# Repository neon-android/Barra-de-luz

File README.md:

# PCB-Mini85-V1.0 
## Placa de control de cuatro pines de entrada y una salida a relevador con funcion corte de 12v o relevador usual
### Controlada por at timy 85 o at tiny 13

# Pin out

## Fabricacion
[Mini-85-V1.0.zip](https://github.com/user-attachments/files/15755527/Mini-85-V1.0.zip)

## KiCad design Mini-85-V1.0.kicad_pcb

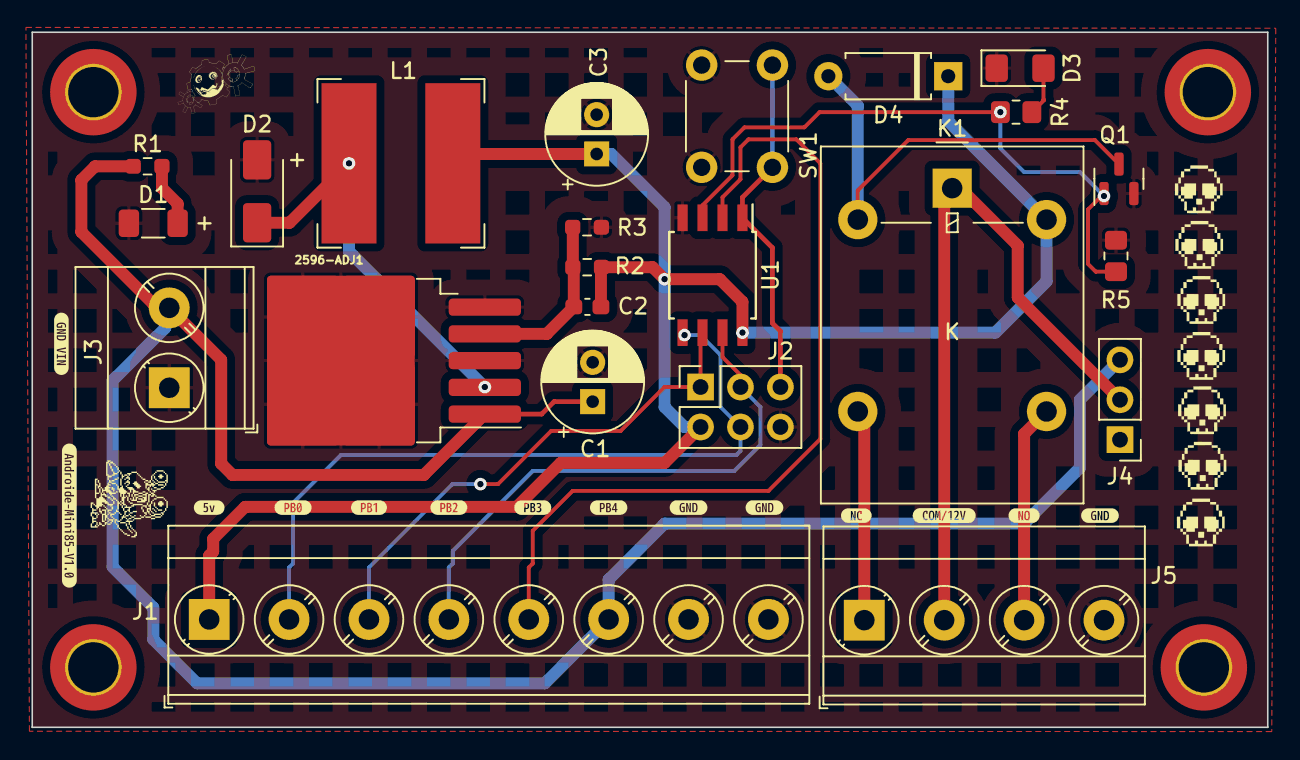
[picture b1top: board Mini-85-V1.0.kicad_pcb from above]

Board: 2 copper layers, 78.6 x 44.2 mm, 41 parts (0 on the bottom side), 17 nets.

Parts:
2596-ADJ1: REGULADOR ADJ; TO-263-5_TabPin3
C1: 470uf 35v; CP_Radial_D6.3mm_P2.50mm
C2: C; C_0603_1608Metric_Pad1.08x0.95mm_HandSolder
C3: 220UF; CP_Radial_D6.3mm_P2.50mm
D1: LED; R_1206_3216Metric_Pad1.30x1.75mm_HandSolder
D2: SS24; D_SMA
D3: LEDRELE; LED_1206_3216Metric_Pad1.42x1.75mm_HandSolder
D4: 1N5400; D_A-405_P7.62mm_Horizontal
H2, H3, H4, H4#2: MountingHole; MountingHole_3.2mm_M3_ISO14580_Pad_TopBottom
J1: Screw_Terminal_01x08; TerminalBlock_Phoenix_MKDS-3-8-5.08_1x08_P5.08mm_Horizontal
J2: AVR-ISP-6; PinSocket_2x03_P2.54mm_Vertical
J3: VIN; TerminalBlock_Phoenix_MKDS-3-2-5.08_1x02_P5.08mm_Horizontal
J4: Conn_01x03_Female; PinHeader_1x03_P2.54mm_Vertical
J5: Screw_Terminal_01x04; TerminalBlock_Phoenix_MKDS-3-4-5.08_1x04_P5.08mm_Horizontal
K1: G5LE-1; Relay_SPDT_Omron-G5LE-1
L1: 330; L_Bourns-SRN1060
Q1: 2N7002H; SOT-23
R1, R2: 1K; R_0603_1608Metric_Pad0.98x0.95mm_HandSolder
R3: 330; R_0603_1608Metric_Pad0.98x0.95mm_HandSolder
R4: 1k; R_0805_2012Metric_Pad1.20x1.40mm_HandSolder
R5: 10K; R_0805_2012Metric_Pad1.20x1.40mm_HandSolder
SW1: SW_Push; SW_PUSH_6mm
U1: ATtiny85-20S; SOIC-8W_5.3x5.3mm_P1.27mm
kibuzzard-65F8FC0E, kibuzzard-65F8FC0E#2, kibuzzard-65F8FC0E#3: G***; kibuzzard-65F8FC0E
kibuzzard-65F8FC7A: G***; kibuzzard-65F8FC7A
kibuzzard-65F8FCA8: G***; kibuzzard-65F8FCA8
kibuzzard-65F8FD72: G***; kibuzzard-65F8FD72
kibuzzard-65F8FDDB: G***; kibuzzard-65F8FDDB
kibuzzard-65F8FDEF: G***; kibuzzard-65F8FDEF
kibuzzard-65F903CA: G***; kibuzzard-65F903CA
kibuzzard-65F9052F: G***; kibuzzard-65F9052F
kibuzzard-66664CF2: G***; kibuzzard-66664CF2
kibuzzard-66664DCB: G***; kibuzzard-66664DCB
kibuzzard-66664E1D: G***; kibuzzard-66664E1D
kibuzzard-66664E03: G***; kibuzzard-66664E03

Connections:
+5V: C2.2, C3.1, D4.1 (K), J1.1, J2.2 (VCC), K1.5, L1.2, R2.1, U1.8 (VCC)
+12V: 2596-ADJ1.1 (VIN), C1.1, J1.6, J3.2, J4.3, R1.1
/MISO: J1.3, J2.1 (MISO), U1.6 (PB1)
/MOSI: J1.2, J2.4 (MOSI), U1.5 (AREF/PB0)
/PB3: J1.5, U1.2 (XTAL1/PB3)
/PB4: Q1.1 (G), R4.1, R5.1, U1.3 (XTAL2/PB4)
/RESET: J2.5 (~RST), SW1.1, U1.1 (~RESET/PB5)
/SCK: J1.4, J2.3 (SCK), U1.7 (PB2)
GND: 2596-ADJ1.3 (GND), 2596-ADJ1.5 (~ON/OFF), C1.2, C3.2, D1.1 (K), D2.2 (A), D3.1 (K), J1.7, J1.8, J2.6 (GND), J3.1, J5.4, Q1.2 (S), R3.2, R5.2, SW1.2, U1.4 (GND)
unnamed: 2596-ADJ1.4 (FB), C2.1, R2.2, R3.1
unnamed: 2596-ADJ1.2 (OUT), D2.1 (K), L1.1
unnamed: D1.2 (A), R1.2
unnamed: D3.2 (A), R4.2
unnamed: D4.2 (A), K1.2, Q1.3 (D)
unnamed: J4.2, J5.2, K1.1
unnamed: J5.1, K1.3
unnamed: J5.3, K1.4

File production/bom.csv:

Designator,Footprint,Quantity,Value,LCSC Part #
2596-ADJ1,TO-263-5_TabPin3,1,REGULADOR ADJ,
C1,CP_Radial_D6.3mm_P2.50mm,1,470uf 35v,
C2,0603,1,C,
C3,CP_Radial_D6.3mm_P2.50mm,1,220UF,
D1,1206,1,LED,
D2,D_SMA,1,SS24,
D3,1206,1,LEDRELE,
D4,D_A-405_P7.62mm_Horizontal,1,1N5400,
"H2, H3, H4_2, H4",MountingHole_3.2mm_M3_ISO14580_Pad_TopBottom,4,MountingHole,
J1,TerminalBlock_Phoenix_MKDS-3-8-5.08_1x08_P5.08mm_Horizontal,1,Screw_Terminal_01x08,
J2,PinSocket_2x03_P2.54mm_Vertical,1,AVR-ISP-6,
J3,TerminalBlock_Phoenix_MKDS-3-2-5.08_1x02_P5.08mm_Horizontal,1,VIN,
J4,PinHeader_1x03_P2.54mm_Vertical,1,Conn_01x03_Female,
J5,TerminalBlock_Phoenix_MKDS-3-4-5.08_1x04_P5.08mm_Horizontal,1,Screw_Terminal_01x04,
K1,Relay_SPDT_Omron-G5LE-1,1,G5LE-1,
L1,L_Bourns-SRN1060,1,330,
Q1,SOT-23,1,2N7002H,
"R1, R2",0603,2,1K,
R3,0603,1,330,
R4,0805,1,1k,
R5,0805,1,10K,
SW1,SW_PUSH_6mm,1,SW_Push,
U1,SOIC-8W_5.3x5.3mm_P1.27mm,1,ATtiny85-20S,

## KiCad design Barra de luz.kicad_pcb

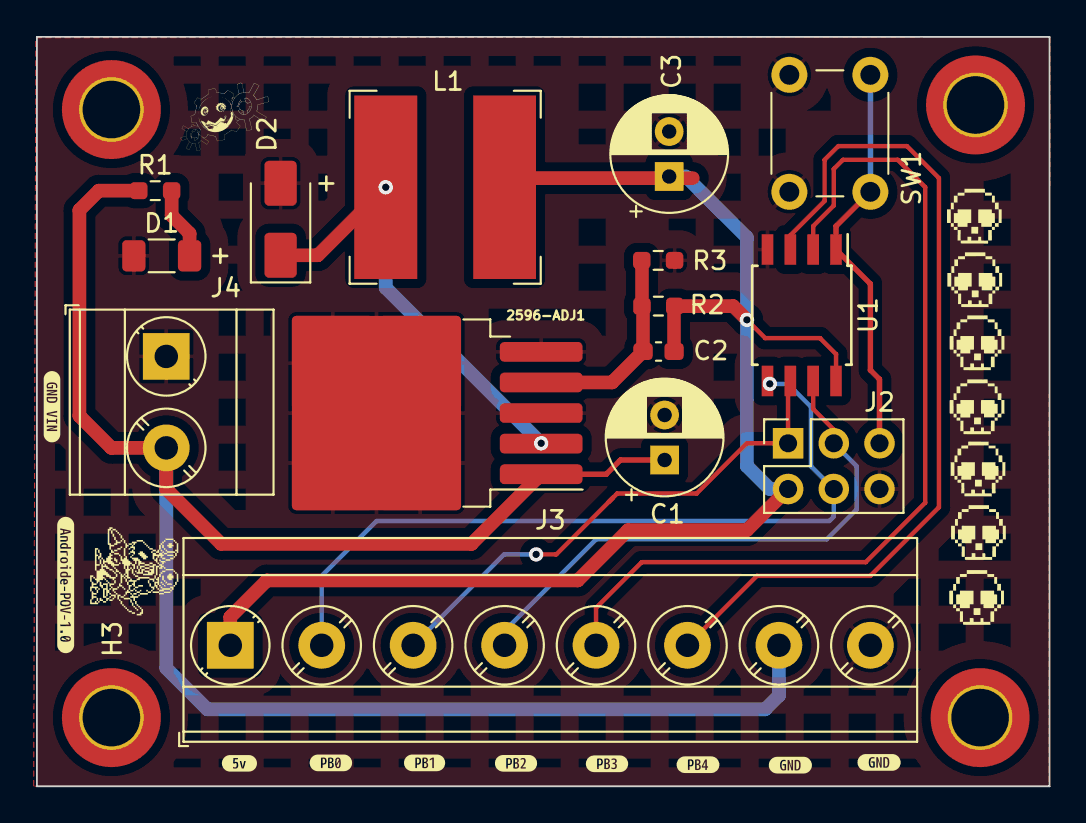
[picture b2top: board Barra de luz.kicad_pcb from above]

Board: 2 copper layers, 56.3 x 41.6 mm, 29 parts (0 on the bottom side), 12 nets.

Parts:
2596-ADJ1: REGULADOR ADJ; TO-263-5_TabPin3
C1: 470uf 35v; CP_Radial_D6.3mm_P2.50mm
C2: C; C_0603_1608Metric_Pad1.08x0.95mm_HandSolder
C3: 220UF; CP_Radial_D6.3mm_P2.50mm
D1: LED; R_1206_3216Metric_Pad1.30x1.75mm_HandSolder
D2: SS24; D_SMA
H3, H4, H4#2, H4#3: MountingHole; MountingHole_3.2mm_M3_ISO14580_Pad_TopBottom
J2: AVR-ISP-6; PinSocket_2x03_P2.54mm_Vertical
J3: Screw_Terminal_01x08; TerminalBlock_Phoenix_MKDS-3-8-5.08_1x08_P5.08mm_Horizontal
J4: VIN; TerminalBlock_Phoenix_MKDS-3-2-5.08_1x02_P5.08mm_Horizontal
L1: 330; L_Bourns-SRN1060
R1, R2: 1K; R_0603_1608Metric_Pad0.98x0.95mm_HandSolder
R3: 330; R_0603_1608Metric_Pad0.98x0.95mm_HandSolder
SW1: SW_Push; SW_PUSH_6mm
U1: ATtiny85-20S; SOIC-8W_5.3x5.3mm_P1.27mm
kibuzzard-65F8F6EE: G***; kibuzzard-65F8F6EE
kibuzzard-65F8FC0E, kibuzzard-65F8FC0E#2: G***; kibuzzard-65F8FC0E
kibuzzard-65F8FC7A: G***; kibuzzard-65F8FC7A
kibuzzard-65F8FCA8: G***; kibuzzard-65F8FCA8
kibuzzard-65F8FD72: G***; kibuzzard-65F8FD72
kibuzzard-65F8FDDB: G***; kibuzzard-65F8FDDB
kibuzzard-65F8FDEF: G***; kibuzzard-65F8FDEF
kibuzzard-65F903CA: G***; kibuzzard-65F903CA
kibuzzard-65F9052F: G***; kibuzzard-65F9052F

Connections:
+5V: C2.2, C3.1, J2.2 (VCC), J3.1, L1.2, R2.1, U1.8 (VCC)
+12V: 2596-ADJ1.1 (VIN), C1.1, J3.7, J4.2, R1.1
/MISO: J2.1 (MISO), J3.3, U1.6 (PB1)
/MOSI: J2.4 (MOSI), J3.2, U1.5 (AREF/PB0)
/PB3: J3.5, U1.2 (XTAL1/PB3)
/PB4: J3.6, U1.3 (XTAL2/PB4)
/RESET: J2.5 (~RST), SW1.1, U1.1 (~RESET/PB5)
/SCK: J2.3 (SCK), J3.4, U1.7 (PB2)
GND: 2596-ADJ1.3 (GND), 2596-ADJ1.5 (~ON/OFF), C1.2, C3.2, D1.1 (K), D2.2 (A), J2.6 (GND), J3.8, J4.1, R3.2, SW1.2, U1.4 (GND)
unnamed: 2596-ADJ1.4 (FB), C2.1, R2.2, R3.1
unnamed: 2596-ADJ1.2 (OUT), D2.1 (K), L1.1
unnamed: D1.2 (A), R1.2

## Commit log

2024-03-24 ajustes para quitar leds y hacer placa mas sencilla
2024-04-02 adaptaciones 12V
2024-06-10 feat se vrea repo
2024-06-17 feat: ajuste de placa
    agujeros de sijecion de placa aplicados
